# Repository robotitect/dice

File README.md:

# Dice

This is an Arduino shield that emulates the rolling of dice.

## Components

0. Arduino Uno R3
1. Vibration/tilt sensor
2. 4-digit 7-segment display
3. 2 position rocker switch
4. LED

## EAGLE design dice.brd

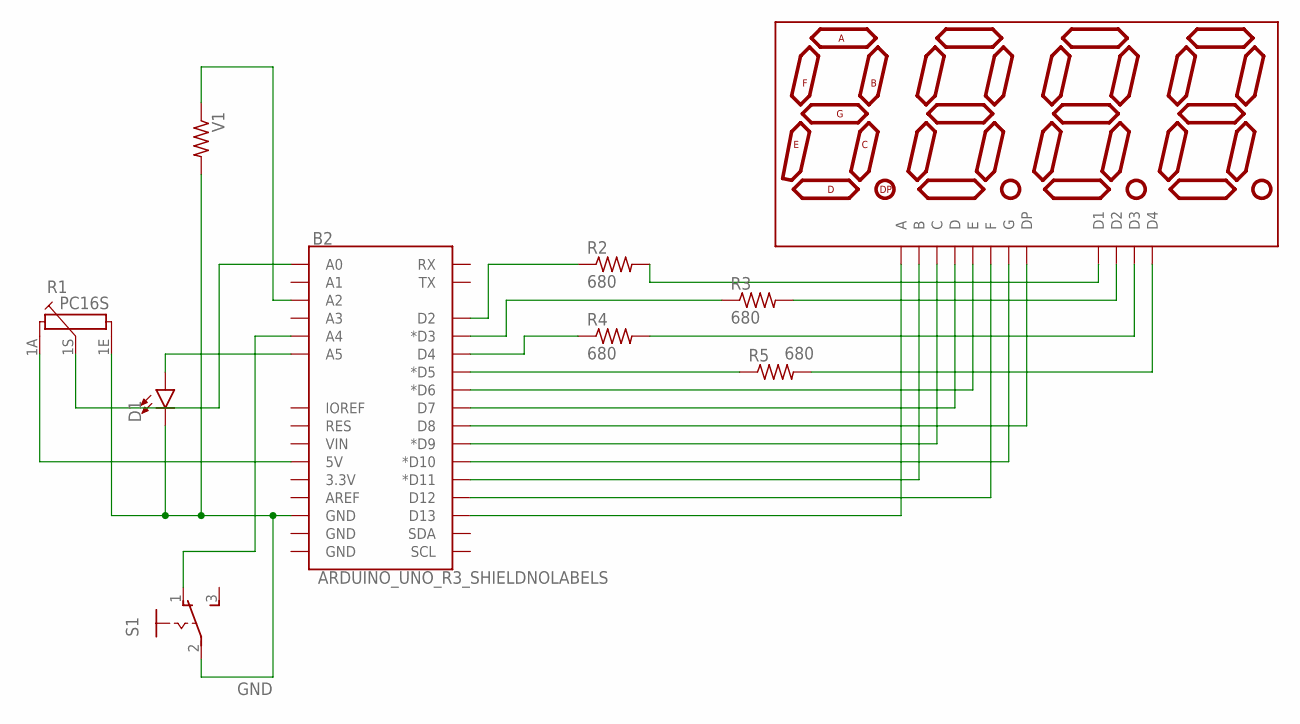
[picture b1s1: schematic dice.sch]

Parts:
B2: ARDUINO_UNO_R3_SHIELDNOLABELS; UNO_R3_SHIELD_NOLABELS
D1: LED5MM; LED_5MM
DISP1: ATA8041AB; 7-SEGMENT-4DIGIT-20MM
R1: PC16S
R2, R3, R4, R5: 680; 0204/7
S1: 255SB
V1: R-US_0414/15; 0414/15

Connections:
A: B2.D13, DISP1.11 (A)
B: B2.D11 (*D11), DISP1.7 (B)
C: B2.D9 (*D9), DISP1.4 (C)
D: B2.D7, DISP1.2 (D)
D1: DISP1.12 (D1), R2.2
D1G: B2.D2, R2.1
D2: DISP1.9 (D2), R3.2
D2G: B2.D3 (*D3), R3.1
D3: DISP1.8 (D3), R4.2
D3G: B2.D4, R4.1
D4: DISP1.6 (D4), R5.2
D4G: B2.D5 (*D5), R5.1
DP: B2.D8, DISP1.3 (DP)
E: B2.D6 (*D6), DISP1.1 (E)
F: B2.D12, DISP1.10 (F)
G: B2.D10 (*D10), DISP1.5 (G)
GND: B2.GND@2 (GND), D1.K (C), R1.1E, S1.2, V1.2
LED: B2.A5, D1.A
POT: B2.A0, R1.1S
SW: B2.A4, S1.1 (O)
VCC: B2.5V, R1.1A
VIBR: B2.A2, V1.1

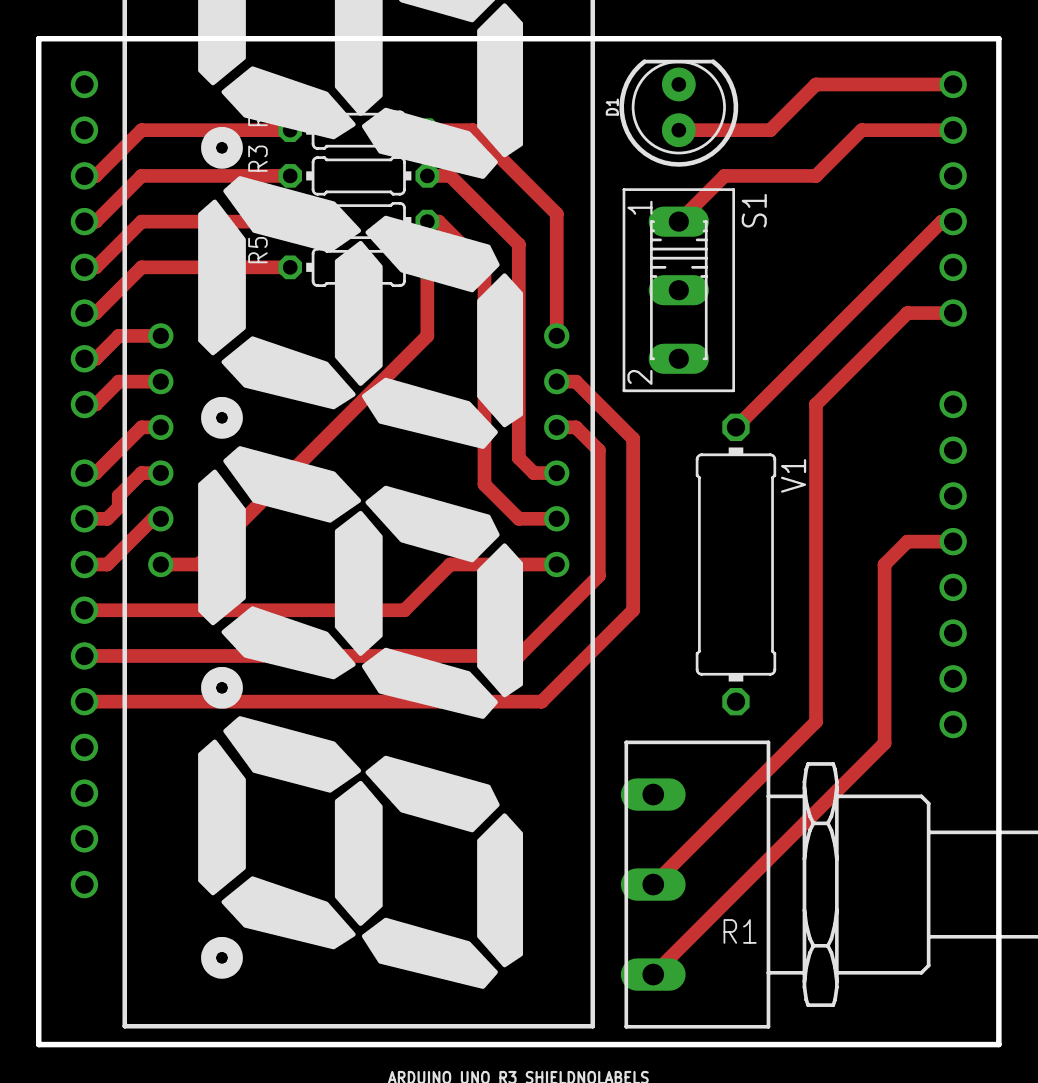
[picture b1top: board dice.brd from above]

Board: 1 copper layer, 53.3 x 55.9 mm, 10 parts (0 on the bottom side), 22 nets.

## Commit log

2018-12-10 First commit: gitignore for EAGLE files
2019-08-03 Add arduino code
2019-08-03 Refresh display using 100Hz timer interrupt
2019-08-04 add schematic and pcb
2023-04-26 Add some useful images
2023-04-26 Bug fixes and add hold switch
    Add hold switch
    Adjust max/min range for pot value so only 1 to 99 shown on the
    display and it doesn't overflow.
    Add delay to main loop so dice "rolling" only happens at 10Hz.
2023-04-26 Connect all traces except GND
2023-04-26 Add GND pours
2023-04-27 Add design rules
2023-04-27 Redo PCB for milling
    Switch to one layer
    Remove ground pours
    Switch to 30mil trace width
    Add circles of trace around every pad
    Reduce hole size on shield and 7 segment display
2023-04-27 Change pin definitions to match PCB
2023-04-27 Fix comment formatting
2023-07-05 Add gerbers to .gitignore
2023-07-05 Update for JLCPCB
    Ground pour
    Remove trace around holes
2023-07-05 Update readme with comps

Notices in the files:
parts and their libraries:
SparkFun-LED: Licensing: Creative Commons ShareAlike 4.0 International - https://creativecommons.org/licenses/by-sa/4.0
